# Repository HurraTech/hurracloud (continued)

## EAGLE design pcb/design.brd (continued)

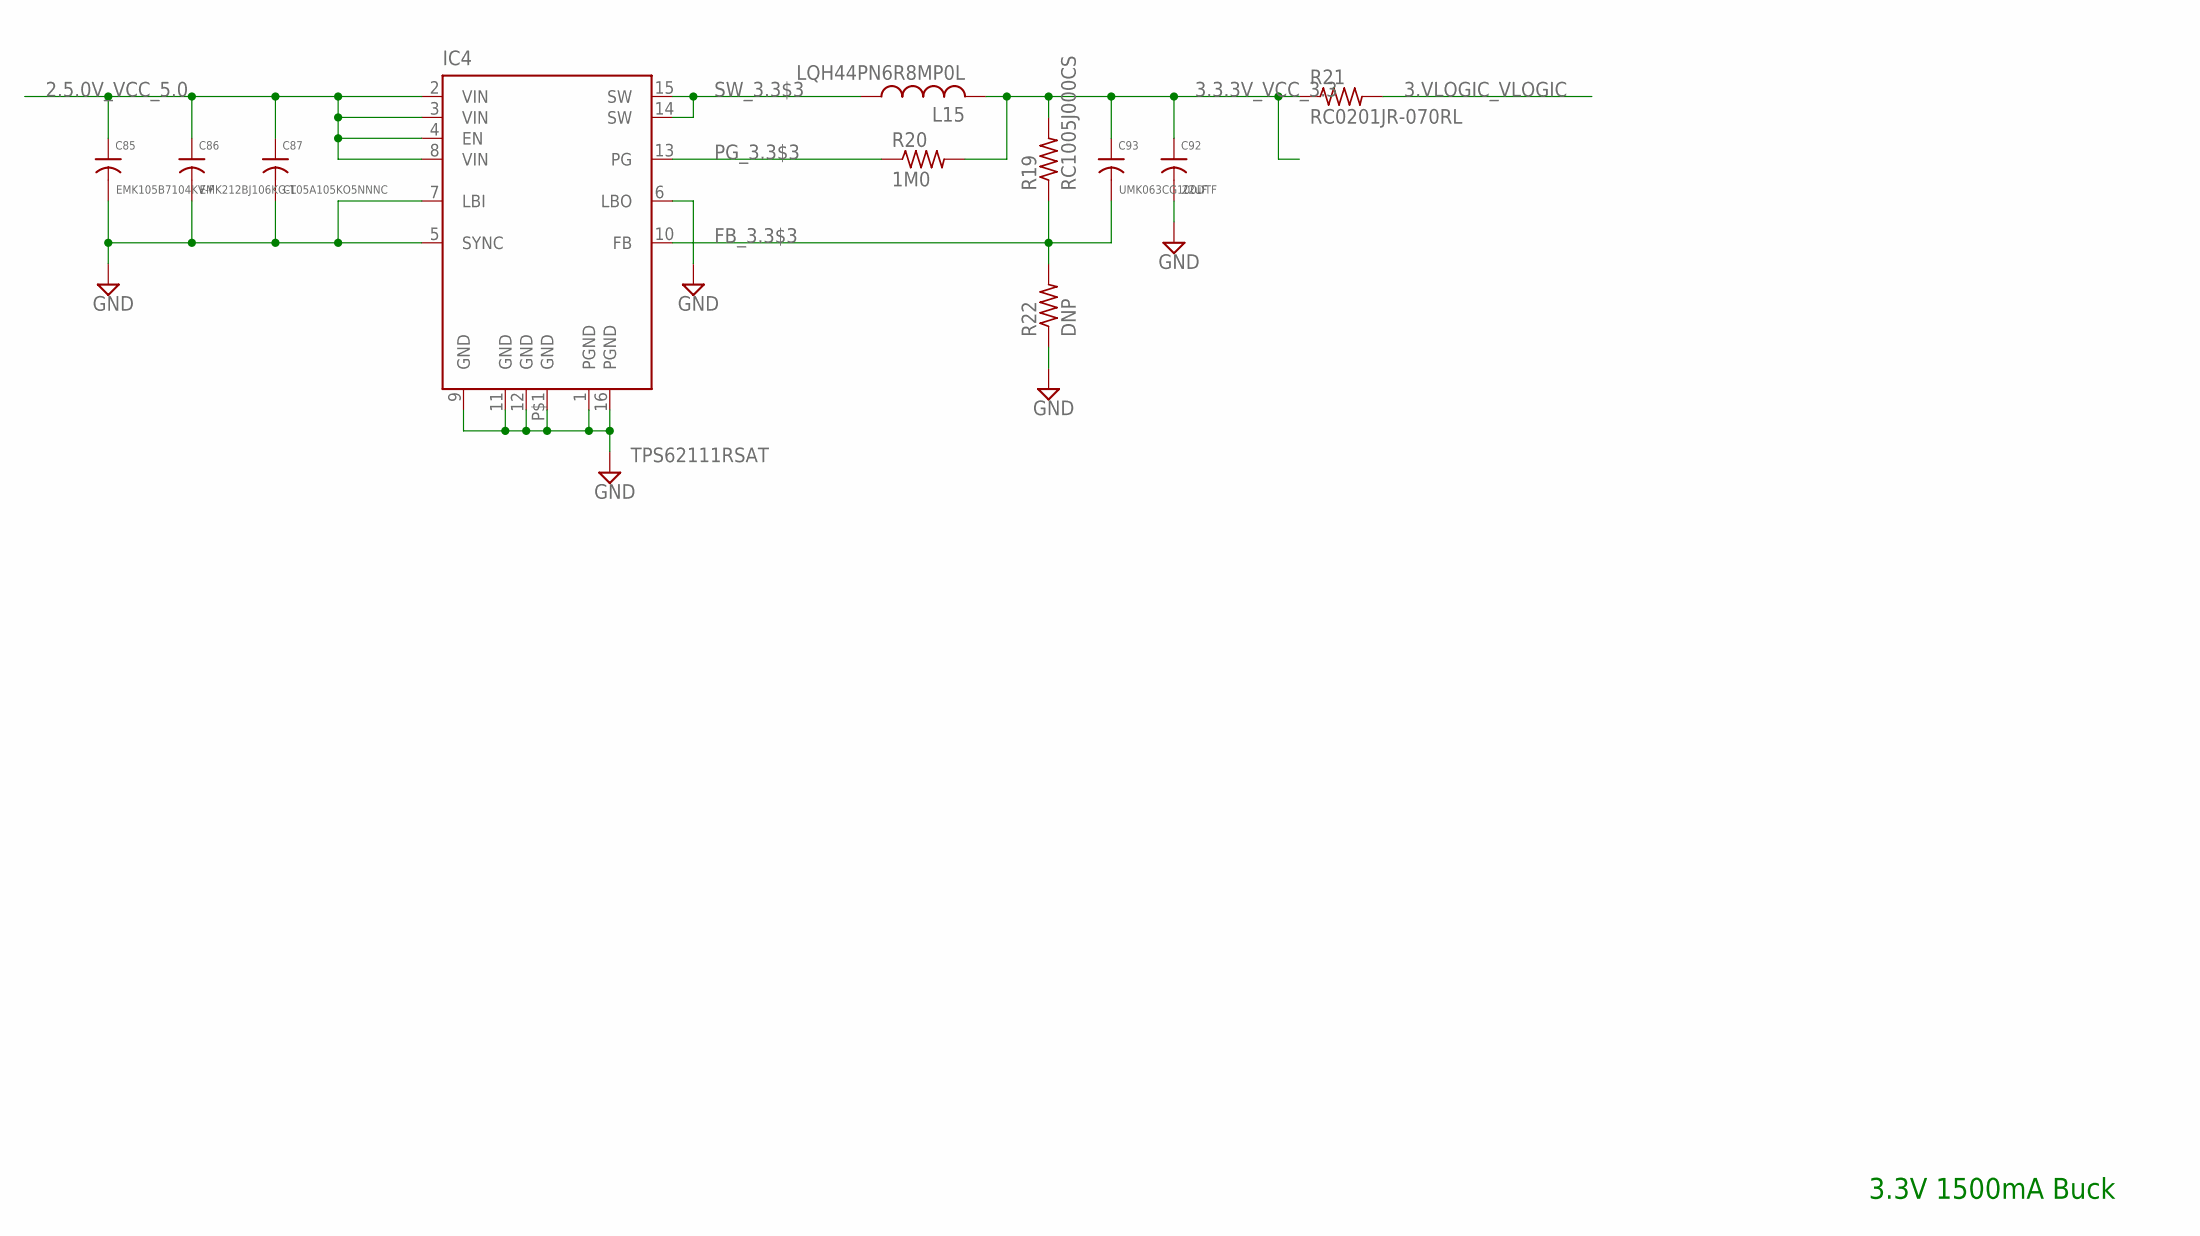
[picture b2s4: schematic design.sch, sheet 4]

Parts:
C85: EMK105B7104KV-F; 0402
C86: EMK212BJ106KG-T; 0805
C87: CL05A105KO5NNNC; 0402
C92: 22uF; 0805
C93: UMK063CG100DTF; 0201
IC4: TPS62111RSAT; PQFP16
L15: LQH44PN6R8MP0L; 1515
R19: RC1005J000CS; 0402
R20: 1M0; 0201
R21: RC0201JR-070RL; 0201
R22: DNP; 0402

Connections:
2.5.0V_VCC_5.0: C85.1, C86.1, C87.1, IC4.2 (VIN), IC4.3 (VIN), IC4.4 (EN), IC4.8 (VIN); also elsewhere on the board
3.3.3V_VCC_3.3: C92.1, C93.1, L15.2, R19.2, R20.2, R21.1; also elsewhere on the board
3.VLOGIC_VLOGIC: R21.2
FB_3.3$3: C93.2, IC4.10 (FB), R19.1, R22.2
GND: C85.2, C86.2, C87.2, C92.2, IC4.1 (PGND), IC4.5 (SYNC), IC4.6 (LBO), IC4.7 (LBI), IC4.9 (GND), IC4.11 (GND), IC4.12 (GND), IC4.16 (PGND), IC4.P$1 (GND), R22.1; also elsewhere on the board
PG_3.3$3: IC4.13 (PG), R20.1
SW_3.3$3: IC4.14 (SW), IC4.15 (SW), L15.1

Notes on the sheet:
3.3V 1500mA Buck

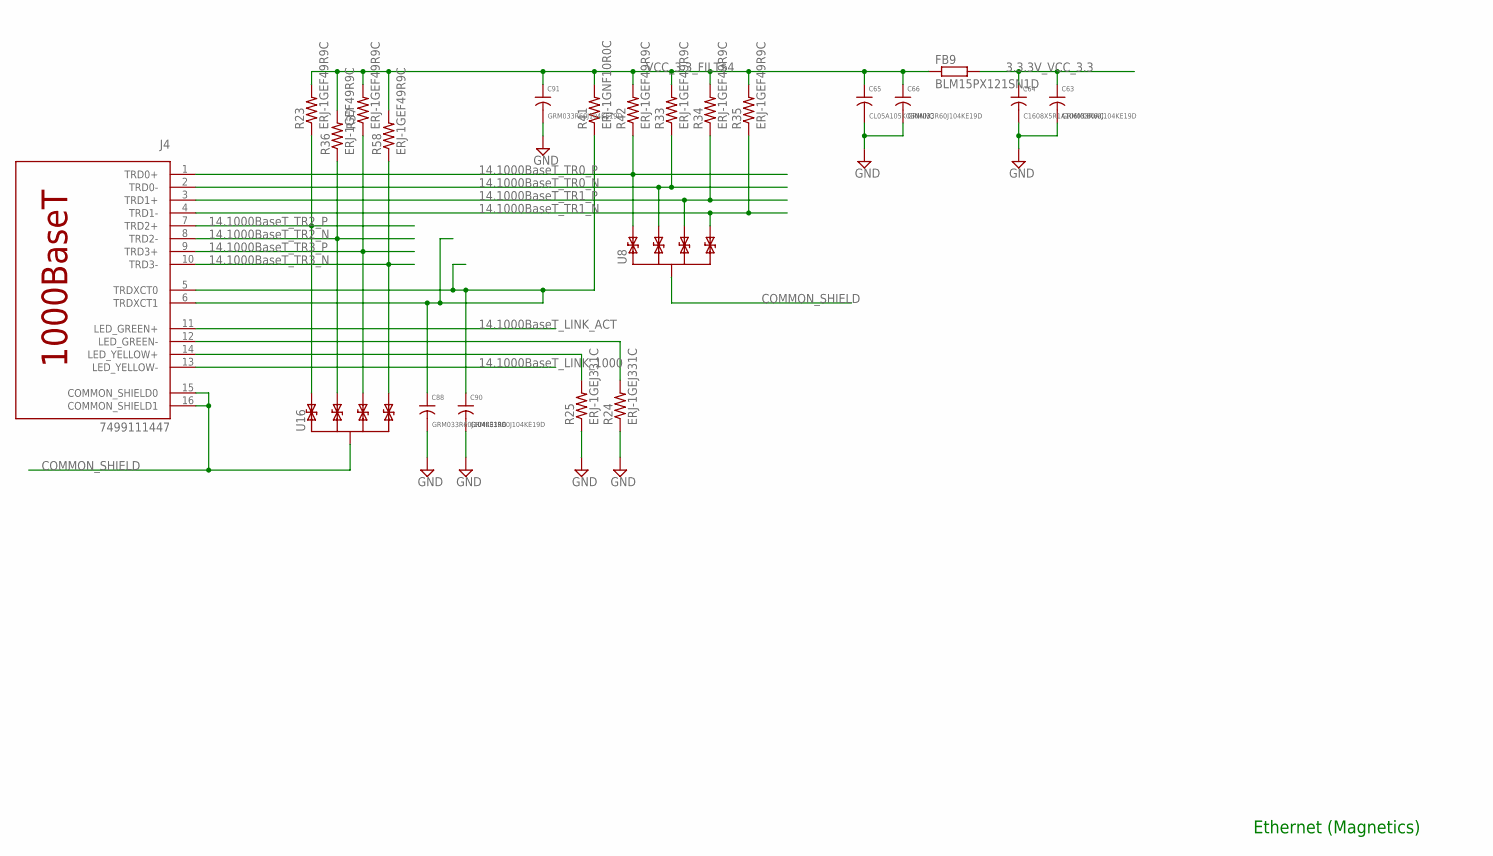
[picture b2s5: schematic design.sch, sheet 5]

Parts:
C63, C66, C88, C90, C91: GRM033R60J104KE19D; 0201
C64: C1608X5R1A106M080AC; 0603
C65: CL05A105KO5NNNC; 0402
FB9: BLM15PX121SN1D; 0402
J4: 7499111447
R23, R33, R34, R35, R36, R37, R42, R58: ERJ-1GEF49R9C; 0201
R24, R25: ERJ-1GEJ331C; 0201
R41: ERJ-1GNF10R0C; 0201
U8, U16: TPD4E02B04DQAR; UFDFN-10

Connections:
3.3.3V_VCC_3.3: C63.1, C64.1, FB9.2; also elsewhere on the board
14.1000BaseT_LINK_1000: J4.13 (LED_YELLOW-); also elsewhere on the board
14.1000BaseT_LINK_ACT: J4.11 (LED_GREEN+); also elsewhere on the board
14.1000BaseT_TR0_N: J4.2 (TRD0-), R33.1, U8.2, U8.9 (P2); also elsewhere on the board
14.1000BaseT_TR0_P: J4.1 (TRD0+), R42.1, U8.1, U8.10 (P1); also elsewhere on the board
14.1000BaseT_TR1_N: J4.4 (TRD1-), R35.1, U8.5 (P4), U8.6 (P4); also elsewhere on the board
14.1000BaseT_TR1_P: J4.3 (TRD1+), R34.1, U8.4 (P3), U8.7 (P3); also elsewhere on the board
14.1000BaseT_TR2_N: J4.8 (TRD2-), R36.1, U16.2, U16.9 (P2); also elsewhere on the board
14.1000BaseT_TR2_P: J4.7 (TRD2+), R23.1, U16.1, U16.10 (P1); also elsewhere on the board
14.1000BaseT_TR3_N: J4.10 (TRD3-), R58.1, U16.5 (P4), U16.6 (P4); also elsewhere on the board
14.1000BaseT_TR3_P: J4.9 (TRD3+), R37.1, U16.4 (P3), U16.7 (P3); also elsewhere on the board
COMMON_SHIELD: J4.15 (COMMON_SHIELD0), J4.16 (COMMON_SHIELD1), U8.3 (SHIELD), U8.8 (SHIELD), U16.3 (SHIELD), U16.8 (SHIELD); also elsewhere on the board
CT0$4: C88.1, C90.1, J4.5 (TRDXCT0), J4.6 (TRDXCT1), R41.1
GND: C63.2, C64.2, C65.2, C66.2, C88.2, C90.2, C91.2, R24.1, R25.1; also elsewhere on the board
LED_GREEN_N$4: J4.12 (LED_GREEN-), R24.2
LED_YELLOW_P$4: J4.14 (LED_YELLOW+), R25.2
VCC_3.3_FILT$4: C65.1, C66.1, C91.1, FB9.1, R23.2, R33.2, R34.2, R35.2, R36.2, R37.2, R41.2, R42.2, R58.2

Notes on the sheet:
Ethernet (Magnetics)

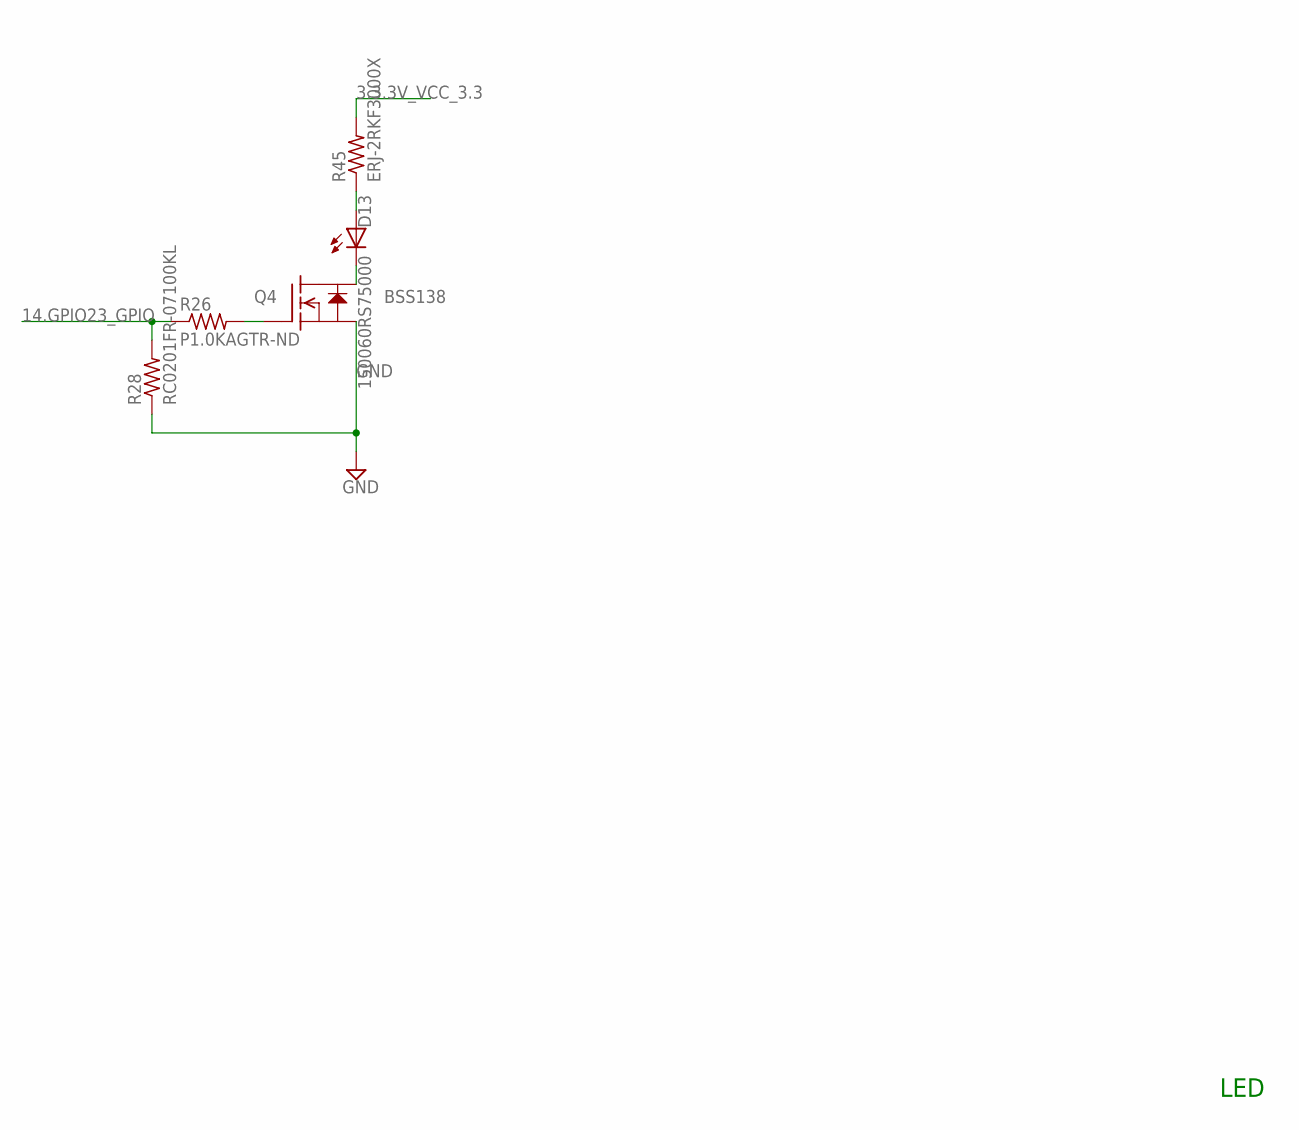
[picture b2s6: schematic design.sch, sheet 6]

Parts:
D13: 150060RS75000; D0603
Q4: BSS138; SOT23
R26: P1.0KAGTR-ND; 0201
R28: RC0201FR-07100KL; 0201
R45: ERJ-2RKF3000X; 0402

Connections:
3.3.3V_VCC_3.3: R45.2; also elsewhere on the board
14.GPIO23_GPIO: R26.1, R28.2; also elsewhere on the board
ANODE$9: D13.A, R45.1
GATE$9: Q4.1 (G), R26.2
GND: Q4.2 (S), R28.1; also elsewhere on the board
LED-$9: D13.C, Q4.3 (D)

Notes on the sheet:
LED

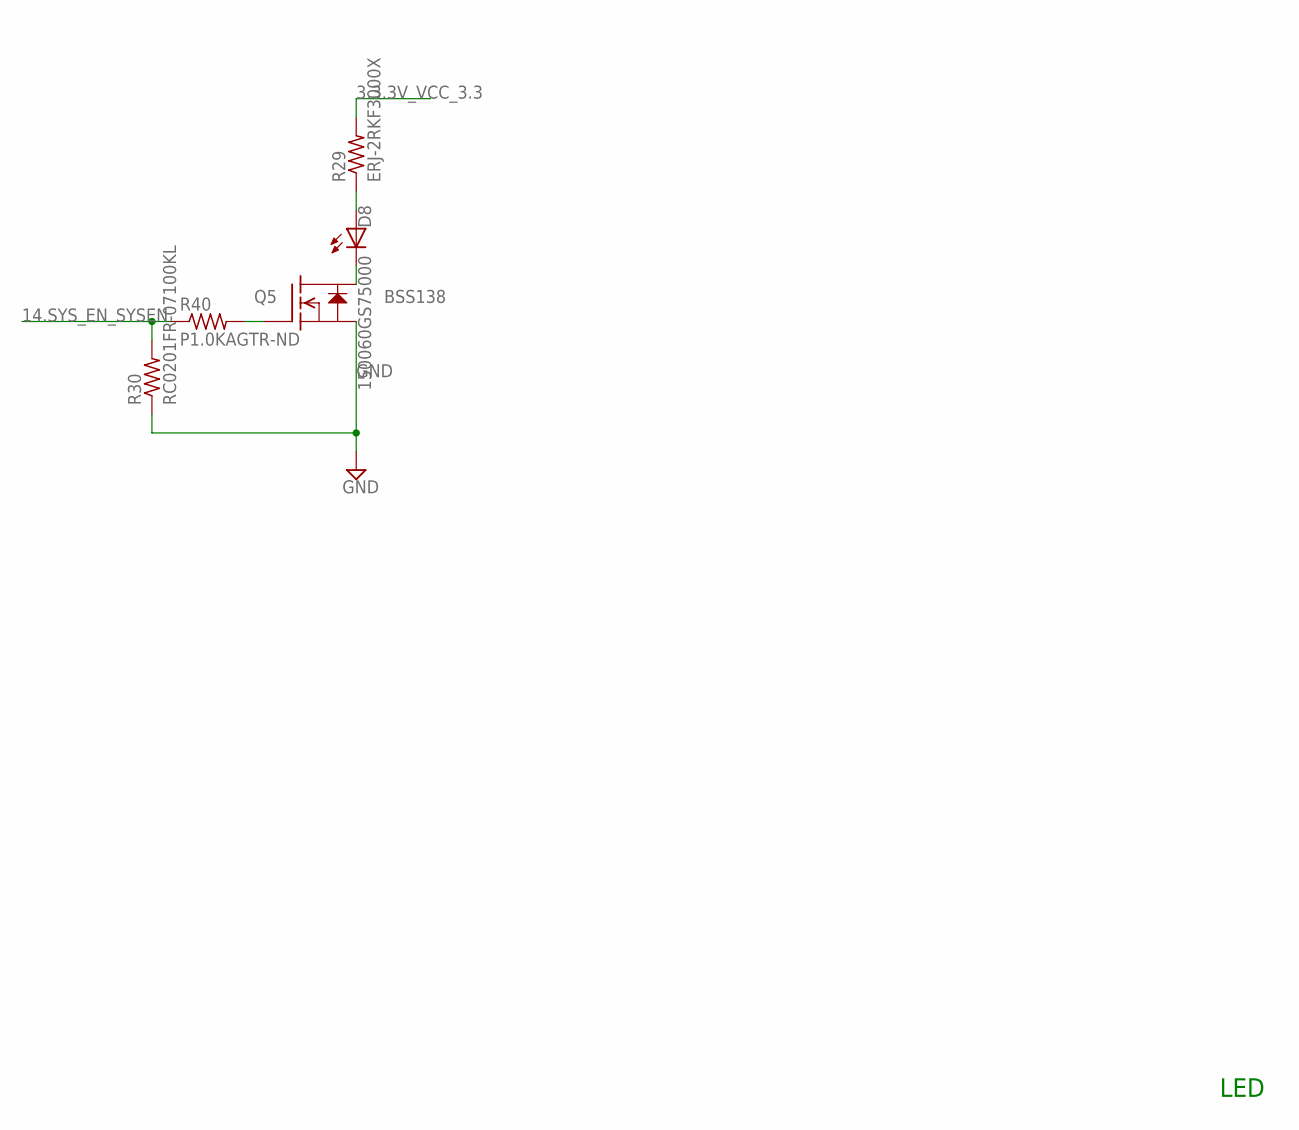
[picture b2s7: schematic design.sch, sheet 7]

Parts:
D8: 150060GS75000; D0603
Q5: BSS138; SOT23
R29: ERJ-2RKF3000X; 0402
R30: RC0201FR-07100KL; 0201
R40: P1.0KAGTR-ND; 0201

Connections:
3.3.3V_VCC_3.3: R29.2; also elsewhere on the board
14.SYS_EN_SYSEN: R30.2, R40.1; also elsewhere on the board
ANODE$10: D8.A, R29.1
GATE$10: Q5.1 (G), R40.2
GND: Q5.2 (S), R30.1; also elsewhere on the board
LED-$10: D8.C, Q5.3 (D)

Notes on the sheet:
LED

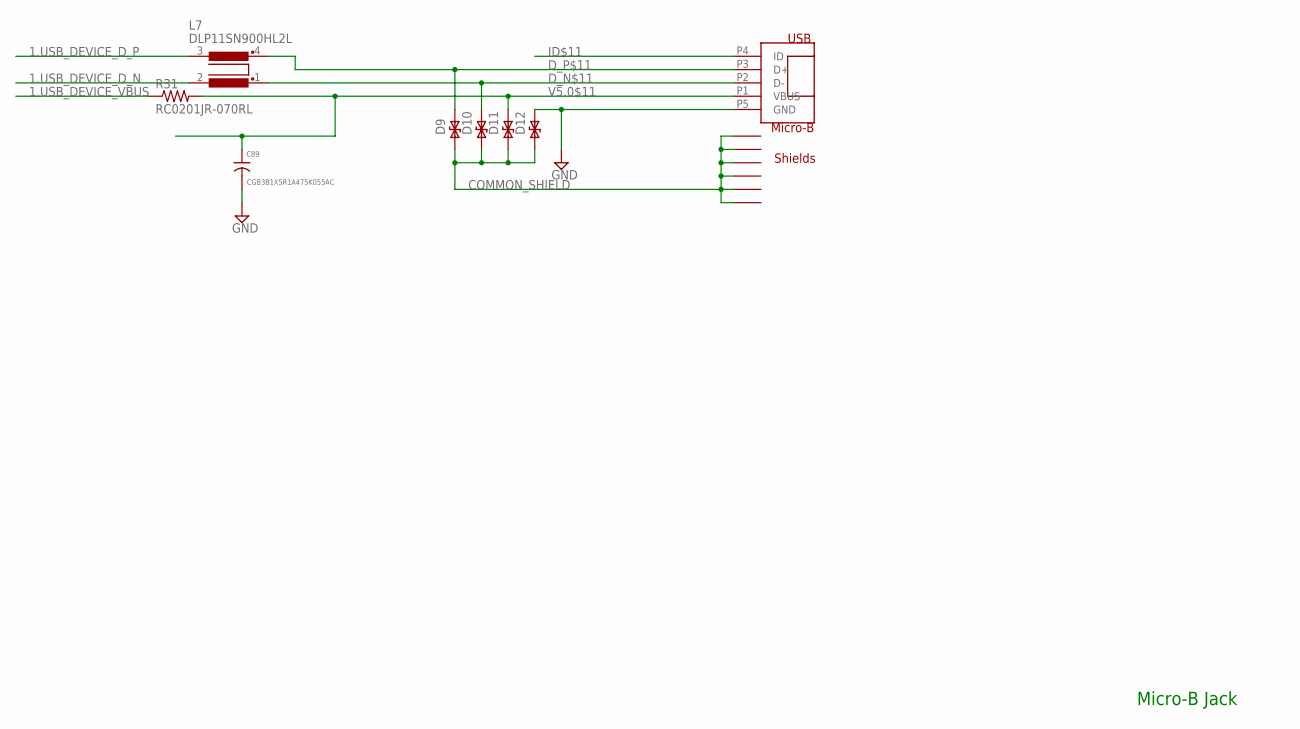
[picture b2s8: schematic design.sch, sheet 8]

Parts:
C89: CGB3B1X5R1A475K055AC; 0603
D9, D10: PS04LTVA1; D0402
D11, D12: B72590D0050A060; D0402
J3: 10118192-0001LF; USB_MICRO_B
L7: DLP11SN900HL2L; 0504-DLP11S
R31: RC0201JR-070RL; 0201

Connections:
1.USB_DEVICE_D_N: L7.2; also elsewhere on the board
1.USB_DEVICE_D_P: L7.3; also elsewhere on the board
1.USB_DEVICE_VBUS: R31.1; also elsewhere on the board
COMMON_SHIELD: D9.P1, D10.P1, D11.P1, D12.P1, J3.COMMON_SHEILD1 (COMMON_SHIELD1), J3.COMMON_SHEILD2 (COMMON_SHIELD2), J3.COMMON_SHEILD3 (COMMON_SHIELD3), J3.COMMON_SHEILD4 (COMMON_SHIELD4), J3.COMMON_SHEILD5 (COMMON_SHIELD5), J3.COMMON_SHEILD6 (COMMON_SHIELD6); also elsewhere on the board
D_N$11: D10.P2, J3.P2 (D-), L7.1
D_P$11: D9.P2, J3.P3 (D+), L7.4
GND: C89.2, D12.P2, J3.P5 (GND); also elsewhere on the board
ID$11: J3.P4 (ID)
V5.0$11: C89.1, D11.P2, J3.P1 (VBUS), R31.2

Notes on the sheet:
Micro-B Jack

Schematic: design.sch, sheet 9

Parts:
C94, C95, C258, C259, C271: GRM033R60J104KE19D; 0201
C257, C261: GRM033R61C103KA12D; 0201
L8, L9, L12, L13: DLP11SN900HL2L; 0504-DLP11S
R43: CRCW040275R0FKEDC; 0402
RP3: DNP; 741X08
U9: TPD13S523PWR; TSSOP16
U14: 685119134923; 47151-001
U$24: TXS0104ERGYR; S-PVQFN-N14

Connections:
2.5.0V_VCC_5.0: C258.1, C259.1, U9.5 (5V_SUPPLY), U$24.14 (VCCB); also elsewhere on the board
14.HDMI0_CEC: RP3.4, U$24.2 (A1); also elsewhere on the board
14.HDMI0_CLOCK_N: L9.2, U9.9 (D3-); also elsewhere on the board
14.HDMI0_CLOCK_P: L9.3, U9.10 (D3+); also elsewhere on the board
14.HDMI0_D0_N: L8.2, U9.11 (D2-); also elsewhere on the board
14.HDMI0_D0_P: L8.3, U9.12 (D2+); also elsewhere on the board
14.HDMI0_D1_N: L13.2, U9.13 (D1-); also elsewhere on the board
14.HDMI0_D1_P: L13.3, U9.14 (D1+); also elsewhere on the board
14.HDMI0_D2_N: L12.2, U9.15 (D0-); also elsewhere on the board
14.HDMI0_D2_P: L12.3, U9.16 (D0+); also elsewhere on the board
14.HDMI0_DDC_SCL: RP3.3, U$24.3 (A2); also elsewhere on the board
14.HDMI0_DDC_SDA: RP3.2, U$24.4 (A3); also elsewhere on the board
14.HDMI0_HPD: RP3.1, U$24.5 (A4); also elsewhere on the board
14.VLOGIC_VLOGIC: C95.1, C257.1, C261.1, C271.1, U$24.1 (VCCA), U$24.8 (OE); also elsewhere on the board
CEC$12: RP3.5, U9.1 (CTRL1), U14.13, U$24.13 (B1)
COMMON_SHIELD: U14.G1 (20), U14.G2 (21), U14.G3 (22), U14.G4 (23); also elsewhere on the board
CON_5V0$12: C94.1, U9.6 (5V_OUT), U14.18
DDC_SCL$12: RP3.6, U9.2 (CTRL2), U14.15, U$24.12 (B2)
DDC_SDA$12: RP3.7, U9.3 (CTRL3), U14.16, U$24.11 (B3)
GND: C94.2, C95.2, C257.2, C258.2, C259.2, C261.2, C271.2, R43.1, U9.8 (GND), U14.2, U14.5, U14.8, U14.11, U14.17, U$24.7 (GND); also elsewhere on the board
HPD$12: RP3.8, U9.4 (CTRL4), U14.19, U$24.10 (B4)
TXD0_CONN_N$12: L8.1, U14.9
TXD0_CONN_P$12: L8.4, U14.7
TXD1_CONN_N$12: L13.1, U14.6
TXD1_CONN_P$12: L13.4, U14.4
TXD2_CONN_N$12: L12.1, U14.3
TXD2_CONN_P$12: L12.4, U14.1
TXDC_CONN_N$12: L9.1, U14.12
TXDC_CONN_P$12: L9.4, U14.10
UTIL$12: R43.2, U9.7 (CTRL5), U14.14

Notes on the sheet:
HDMI

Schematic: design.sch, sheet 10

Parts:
C256: GRM033R60J104KE19D; 0201
R38: RC0201FR-0710KL; 0201
R39: RC0201JR-070RL; 0201
RP1, RP2: DNP; RP741X083
U19: TS3A5223RSWR; UQFN-10

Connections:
13.UART1_RXD: RP1.1, U19.7 (NC2); also elsewhere on the board
13.UART1_TXD: RP1.2, U19.5 (NC1); also elsewhere on the board
13.UART2_RXD: RP2.4, U19.10 (NO2); also elsewhere on the board
13.UART2_TXD: RP2.3, U19.2 (NO1); also elsewhere on the board
13.VLOGIC_OUT_VLOGIC: R39.2; also elsewhere on the board
14.UART0_RXD: RP1.8, RP2.5, U19.9 (COM2); also elsewhere on the board
14.UART0_TXD: RP1.7, RP2.6, U19.3 (COM1); also elsewhere on the board
14.USB3_CC2_GPIO: R38.2, U19.4 (SEL1), U19.8 (SEL2); also elsewhere on the board
14.VLOGIC_VLOGIC: C256.1, R39.1, U19.1 (VCC); also elsewhere on the board
GND: C256.2, R38.1, U19.6 (GND); also elsewhere on the board

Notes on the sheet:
Quad 2 Input MUX

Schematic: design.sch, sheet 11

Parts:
J2, J5: DF40C-100DS-0.4V(51); HRS_DF40C-100DS-0.4V(51)
MP1, MP2, MP3, MP4: 9774015151R; WA-SMSI_9774___151
Q1: BSS138; SOT23
Q2, Q3: FDN360P; SOT23
R44, R49, R50: RC0201JR-070RL; 0201
R48: DNP; 0201
R51: RC0201FR-0710KL; 0201

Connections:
1.8V_OUT$14: J5.88, J5.90, R48.1
2.5.0V_VCC_5.0: J5.77, J5.79, J5.81, J5.83, J5.85, J5.87; also elsewhere on the board
3.3V_OUT$14: J5.84, J5.86, Q2.3 (D), R44.1, R50.1
14.3.3V_VCC_3.3: Q3.3 (D), R49.2; also elsewhere on the board
14.1000BaseT_LINK_100: J5.19
14.1000BaseT_LINK_1000: J5.17; also elsewhere on the board
14.1000BaseT_LINK_ACT: J5.15; also elsewhere on the board
14.1000BaseT_TR0_N: J5.10; also elsewhere on the board
14.1000BaseT_TR0_P: J5.12; also elsewhere on the board
14.1000BaseT_TR1_N: J5.6; also elsewhere on the board
14.1000BaseT_TR1_P: J5.4; also elsewhere on the board
14.1000BaseT_TR2_N: J5.9; also elsewhere on the board
14.1000BaseT_TR2_P: J5.11; also elsewhere on the board
14.1000BaseT_TR3_N: J5.5; also elsewhere on the board
14.1000BaseT_TR3_P: J5.3; also elsewhere on the board
14.GPIO2_GPIO: J5.58; also elsewhere on the board
14.GPIO3_GPIO: J5.56; also elsewhere on the board
14.GPIO4_GPIO: J5.54; also elsewhere on the board
14.GPIO5_GPIO: J5.34; also elsewhere on the board
14.GPIO6_GPIO: J5.30; also elsewhere on the board
14.GPIO7_GPIO: J5.37; also elsewhere on the board
14.GPIO8_GPIO: J5.39; also elsewhere on the board
14.GPIO9_GPIO: J5.40; also elsewhere on the board
14.GPIO10_GPIO: J5.44; also elsewhere on the board
14.GPIO11_GPIO: J5.38; also elsewhere on the board
14.GPIO12_GPIO: J5.31; also elsewhere on the board
14.GPIO13_GPIO: J5.28; also elsewhere on the board
14.GPIO16_GPIO: J5.29; also elsewhere on the board
14.GPIO17_GPIO: J5.50; also elsewhere on the board
14.GPIO18_GPIO: J5.49; also elsewhere on the board
14.GPIO19_GPIO: J5.26; also elsewhere on the board
14.GPIO20_GPIO: J5.27; also elsewhere on the board
14.GPIO21_GPIO: J5.25; also elsewhere on the board
14.GPIO22_GPIO: J5.46; also elsewhere on the board
14.GPIO23_GPIO: J5.47; also elsewhere on the board
14.GPIO24_GPIO: J5.45; also elsewhere on the board
14.GPIO25_GPIO: J5.41; also elsewhere on the board
14.GPIO26_GPIO: J5.24; also elsewhere on the board
14.GPIO27_GPIO: J5.48; also elsewhere on the board
14.HDMI0_CEC: J2.51; also elsewhere on the board
14.HDMI0_CLOCK_N: J2.90; also elsewhere on the board
14.HDMI0_CLOCK_P: J2.88; also elsewhere on the board
14.HDMI0_D0_N: J2.84; also elsewhere on the board
14.HDMI0_D0_P: J2.82; also elsewhere on the board
14.HDMI0_D1_N: J2.78; also elsewhere on the board
14.HDMI0_D1_P: J2.76; also elsewhere on the board
14.HDMI0_D2_N: J2.72; also elsewhere on the board
14.HDMI0_D2_P: J2.70; also elsewhere on the board
14.HDMI0_DDC_SCL: J2.100; also elsewhere on the board
14.HDMI0_DDC_SDA: J2.99; also elsewhere on the board
14.HDMI0_HPD: J2.53; also elsewhere on the board
14.I2C_ID_SCL: J5.35; also elsewhere on the board
14.I2C_ID_SDA: J5.36; also elsewhere on the board
14.PCIE_CLKREQ_GPIO: J2.2; also elsewhere on the board
14.PCIE_CLK_N: J2.12; also elsewhere on the board
14.PCIE_CLK_P: J2.10; also elsewhere on the board
14.PCIE_RST_GPIO: J2.9; also elsewhere on the board
14.PCIE_RX0_N: J2.18; also elsewhere on the board
14.PCIE_RX0_P: J2.16; also elsewhere on the board
14.PCIE_TX0_N: J2.24; also elsewhere on the board
14.PCIE_TX0_P: J2.22; also elsewhere on the board
14.SYS_EN_SYSEN: J5.100, Q1.1 (G), R51.2; also elsewhere on the board
14.UART0_RXD: J5.51; also elsewhere on the board
14.UART0_TXD: J5.55; also elsewhere on the board
14.USB3_CC1_GPIO: J5.94; also elsewhere on the board
14.USB3_CC2_GPIO: J5.96; also elsewhere on the board
14.USB_HOST_DRV_VBUS: R50.2; also elsewhere on the board
14.USB_HOST_D_N: J2.3; also elsewhere on the board
14.USB_HOST_D_P: J2.5; also elsewhere on the board
14.VLOGIC_VLOGIC: R49.1; also elsewhere on the board
14.nRESET_NRESET: J5.92; also elsewhere on the board
!RPIBOOT$14: J5.93
DS_LOAD$14: Q2.2 (S), Q3.2 (S)
EEPROM_!WP: J5.20
ETH_SYNC_IN: J5.16
ETH_SYNC_OUT: J5.18
GLOBAL_EN: J5.99
GND: J2.7, J2.8, J2.13, J2.14, J2.19, J2.20, J2.25, J2.26, J2.31, J2.32, J2.37, J2.38, J2.44, J2.50, J2.55, J2.56, J2.61, J2.62, J2.67, J2.68, J2.73, J2.74, J2.79, J2.80, J2.85, J2.86, J2.91, J2.92, J2.97, J2.98, J5.1, J5.2, J5.7, J5.8, J5.13, J5.14, J5.22, J5.23, J5.32, J5.33, J5.42, J5.43, J5.52, J5.53, J5.59, J5.60, J5.65, J5.66, J5.71, J5.74, J5.98, MP1.1, MP2.1, MP3.1, MP4.1, Q1.2 (S), R51.1; also elsewhere on the board
GPIO_VREF$14: J5.78, R44.2, R48.2; also elsewhere on the board
LOAD_GATE$14: Q1.3 (D), Q2.1 (G), Q3.1 (G)
PI_!LED_ACT: J5.21
PI_LED_!PWR: J5.95
SD_CLK: J5.57
SD_CMD: J5.62
SD_DAT0: J5.63
SD_DAT1: J5.67
SD_DAT2: J5.69
SD_DAT3: J5.61
SD_DAT4: J5.68
SD_DAT5: J5.64
SD_DAT6: J5.72
SD_DAT7: J5.70
SD_PWR_ON: J5.75
SD_VDD_OV: J5.73
VDAC_COMP: J2.11

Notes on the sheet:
Raspberry Pi CM4
GPIO
High Speed

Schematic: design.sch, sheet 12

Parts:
C260: GRM033R60J104KE19D; 0201
IC5: CAT24C256YI-GT3; TSSOP8
R52, R53, R54: RC0201FR-07100KL; 0201
R56, R57: ERJ-1GNJ152C; 0201

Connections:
14.I2C_ID_SCL: IC5.6 (SCL), R57.1; also elsewhere on the board
14.I2C_ID_SDA: IC5.5 (SDA), R56.1; also elsewhere on the board
A0$14: IC5.1 (A0), R54.2
A1$14: IC5.2 (A1), R53.2
A2$14: IC5.3 (A2), R52.2
GND: C260.2, IC5.4 (GND), IC5.7 (WP), R52.1, R53.1; also elsewhere on the board
GPIO_VREF$14: C260.1, IC5.8 (VCC), R54.1, R56.2, R57.2; also elsewhere on the board

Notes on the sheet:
Raspberry Pi CM4

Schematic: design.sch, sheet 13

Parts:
U12: 67996-140HLF; 2X20

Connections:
2.5.0V_VCC_5.0: U12.2, U12.4; also elsewhere on the board
3.3.3V_VCC_3.3: U12.17; also elsewhere on the board
13.UART1_RXD: U12.10; also elsewhere on the board
13.UART1_TXD: U12.8; also elsewhere on the board
14.3.3V_VCC_3.3: U12.1; also elsewhere on the board
14.GPIO2_GPIO: U12.3; also elsewhere on the board
14.GPIO3_GPIO: U12.5; also elsewhere on the board
14.GPIO4_GPIO: U12.7; also elsewhere on the board
14.GPIO5_GPIO: U12.29; also elsewhere on the board
14.GPIO6_GPIO: U12.31; also elsewhere on the board
14.GPIO7_GPIO: U12.26; also elsewhere on the board
14.GPIO8_GPIO: U12.24; also elsewhere on the board
14.GPIO9_GPIO: U12.21; also elsewhere on the board
14.GPIO10_GPIO: U12.19; also elsewhere on the board
14.GPIO11_GPIO: U12.23; also elsewhere on the board
14.GPIO12_GPIO: U12.32; also elsewhere on the board
14.GPIO13_GPIO: U12.33; also elsewhere on the board
14.GPIO16_GPIO: U12.36; also elsewhere on the board
14.GPIO17_GPIO: U12.11; also elsewhere on the board
14.GPIO18_GPIO: U12.12; also elsewhere on the board
14.GPIO19_GPIO: U12.35; also elsewhere on the board
14.GPIO20_GPIO: U12.38; also elsewhere on the board
14.GPIO21_GPIO: U12.40; also elsewhere on the board
14.GPIO22_GPIO: U12.15; also elsewhere on the board
14.GPIO23_GPIO: U12.16; also elsewhere on the board
14.GPIO24_GPIO: U12.18; also elsewhere on the board
14.GPIO25_GPIO: U12.22; also elsewhere on the board
14.GPIO26_GPIO: U12.37; also elsewhere on the board
14.GPIO27_GPIO: U12.13; also elsewhere on the board
14.I2C_ID_SCL: U12.28; also elsewhere on the board
14.I2C_ID_SDA: U12.27; also elsewhere on the board
GND: U12.6, U12.9, U12.14, U12.20, U12.25, U12.30, U12.34, U12.39; also elsewhere on the board

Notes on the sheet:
40-Pin Header

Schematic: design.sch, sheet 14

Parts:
C41, C42, C43, C44, C253, C254, C263, C264, C265, C266, C267, C268, C269, C273, C280, C281, C286, C287, C288, C289: GRM033R60J104KE19D; 0201
C45, C46: C1608X5R1A106M080AC; 0603
C158, C167: CGB3B1X5R1A475K055AC; 0603
C270: GRM033R71A682KA01D; 0201
C282, C283: C1608X5R1C475K080AC; 0603
C285: UMK063CG100DTF; 0201
R27, R55: RC0201FR-0710KL; 0201
R32: RC0201FR-0712K1L; 0201
R47: RC0201FR-07100KL; 0201
U10: ASM1142; QFN64-9X9MM-FT2232HQ
U18: ADP1740ACPZ-1.2-R7; LFCSPWQ16
Y3: ABM8G-20.000MHZ-18-D2Y-T; CRYSTAL-3225

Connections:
3.3.3V_VCC_3.3: C41.1, C42.1, C45.1, C158.1, C267.1, C268.1, C269.1, C280.1, C286.1, C287.1, R27.2, R47.2, R55.2, U10.4 (VCC), U10.20 (VCCSUS), U10.24 (VCCSUS), U10.32 (VCC), U10.38 (VCCU), U10.44 (VCCU), U10.55 (VCCP), U10.62 (VCCP), U18.1 (VIN), U18.2 (VIN), U18.3 (VIN), U18.4 (EN), U18.15 (VIN), U18.16 (VIN); also elsewhere on the board
14.PCIE_CLKREQ_GPIO: R27.1, U10.9 (!PORST); also elsewhere on the board
14.PCIE_CLK_N: U10.49 (PCIE_REFCLK_N); also elsewhere on the board
14.PCIE_CLK_P: U10.48 (PCIE_REFCLK_P); also elsewhere on the board
14.PCIE_RST_GPIO: R55.1, U10.30 (!PERST); also elsewhere on the board
14.PCIE_RX0_N: C273.1; also elsewhere on the board
14.PCIE_RX0_P: C263.1; also elsewhere on the board
14.PCIE_TX0_N: C253.1; also elsewhere on the board
14.PCIE_TX0_P: C254.1; also elsewhere on the board
16.USBH1_DRV_VBUS: U10.26 (PWRON1)
16.USBH1_D_N: U10.22 (USB1_N); also elsewhere on the board
16.USBH1_D_P: U10.23 (USB1_P); also elsewhere on the board
16.USBH1_NOC: U10.28 (!OC1)
16.USBH1_SSRX_N: U10.46 (USB1_SSRX_N); also elsewhere on the board
16.USBH1_SSRX_P: U10.45 (USB1_SSRX_P); also elsewhere on the board
16.USBH1_SSTX_N: U10.43 (USB1_SSTX_N); also elsewhere on the board
16.USBH1_SSTX_P: U10.42 (USB1_SSTX_P); also elsewhere on the board
16.USBH2_DRV_VBUS: U10.27 (PWRON2); also elsewhere on the board
16.USBH2_D_N: U10.18 (USB2_N); also elsewhere on the board
16.USBH2_D_P: U10.19 (USB2_P); also elsewhere on the board
16.USBH2_NOC: U10.29 (!OC2); also elsewhere on the board
16.USBH2_SSRX_N: U10.37 (USB2_SSRX_N); also elsewhere on the board
16.USBH2_SSRX_P: U10.36 (USB2_SSRX_P); also elsewhere on the board
16.USBH2_SSTX_N: U10.40 (USB2_SSTX_N); also elsewhere on the board
16.USBH2_SSTX_P: U10.39 (USB2_SSTX_P); also elsewhere on the board
!SPI_CS$16: U10.7 (!SPI_CS)
GND: C41.2, C42.2, C43.2, C44.2, C45.2, C46.2, C158.2, C167.2, C264.2, C265.2, C266.2, C267.2, C268.2, C269.2, C270.2, C280.2, C281.2, C282.2, C283.2, C286.2, C287.2, C288.2, C289.2, R32.1, U10.15 (GND), U10.65 (GND), U10.EPAD1 (GND), U10.EPAD2 (GND), U10.EPAD3 (GND), U10.EPAD4 (GND), U10.EPAD5 (GND), U10.EPAD6 (GND), U10.EPAD7 (GND), U10.EPAD8 (GND), U10.EPAD9 (GND), U10.EPAD10 (GND), U10.EPAD11 (GND), U10.EPAD12 (GND), U18.6 (GND), U18.EP (GND), U18.EP1 (GND), U18.EP2 (GND), U18.EP3 (GND), U18.EP4 (GND), Y3.2, Y3.4; also elsewhere on the board
PCIE_RX0_N$16: C273.2, U10.57 (PCIE_TX0_N)
PCIE_RX0_P$16: C263.2, U10.56 (PCIE_TX0_P)
PCIE_TX0_N$16: C253.2, U10.54 (PCIE_RX0_N)
PCIE_TX0_P$16: C254.2, U10.53 (PCIE_RX0_P)
REXT$16: R32.2, U10.59 (REXT)
SPI_CLK$16: U10.5 (SPI_CLK)
SPI_DI$16: U10.8 (SPI_DI)
SPI_DO$16: U10.6 (SPI_DO)
UART_RX$16: U10.10 (UART_RX)
UART_TX$16: U10.11 (UART_TX)
V1.2$16: C43.1, C44.1, C46.1, C167.1, C264.1, C265.1, C266.1, C281.1, C282.1, C283.1, C288.1, C289.1, U10.1 (VDD), U10.12 (VDD), U10.21 (VDDSUS), U10.33 (VDD), U10.34 (VDDSUS), U10.35 (VDDU), U10.41 (VDDU), U10.47 (VDDU), U10.52 (VDDP), U10.58 (VDDP), U18.9 (SENSE), U18.10 (VOUT), U18.11 (VOUT), U18.12 (VOUT), U18.13 (VOUT), U18.14 (VOUT)
VCC1V1_SS$16: C270.1, U18.7 (SS)
VCC_1V2_PG$16: R47.1, U18.5 (PG)
XI$16: C285.2, U10.51 (XI), Y3.1
XO$16: C285.1, U10.50 (XO), Y3.3

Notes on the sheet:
PCIe to USB3.0

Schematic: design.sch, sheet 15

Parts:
C272: GRM033R60J104KE19D; 0201
C274: GRM033R61C103KA12D; 0201
C275: C1608X5R1A106M080AC; 0603
C276, C278: DNP; 1206
C277, C279: GRM31CR60J227ME11L; 1206
D2, D5, D6, D15: PS04LTVA1; D0402
D3, D4, D7: B72590D0050A060; D0402
FB11, FB12, FB13, FB14: BLM15PX121SN1D; 0402
K1: 61400826021
L10, L11: DLP11SN900HL2L; 0504-DLP11S
U11: TPS2052BDGNR; MSOP8-PAD

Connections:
2.5.0V_VCC_5.0: C272.1, FB11.1; also elsewhere on the board
18.USBH1_DRV_VBUS: U11.3 (EN1); also elsewhere on the board
18.USBH1_D_N: L10.2; also elsewhere on the board
18.USBH1_D_P: L10.3; also elsewhere on the board
18.USBH1_NOC: U11.8 (NOC1); also elsewhere on the board
18.USBH1_VBUS: D3.P2, FB14.2, U11.7 (OUT1)
18.USBH2_DRV_VBUS: U11.4 (EN2); also elsewhere on the board
18.USBH2_D_N: L11.2; also elsewhere on the board
18.USBH2_D_P: L11.3; also elsewhere on the board
18.USBH2_NOC: U11.5 (NOC2); also elsewhere on the board
18.USBH2_VBUS: D7.P2, FB13.2, U11.6 (OUT2)
A_GNDF$17: C274.1, D4.P2, FB12.2, K1.A4 (GND), K1.B4 (GND)
A_USB_D_N$17: D15.P2, K1.A2 (D-), L10.1
A_USB_D_P$17: D2.P2, K1.A3 (D+), L10.4
A_VBUS_$17: C276.1, C277.1, FB14.1, K1.A1 (VCC)
B_USB_D_N$17: D5.P2, K1.B2 (D-), L11.1
B_USB_D_P$17: D6.P2, K1.B3 (D+), L11.4
B_VBUS_$17: C278.1, C279.1, FB13.1, K1.B1 (VCC)
COMMON_SHIELD: D2.P1, D3.P1, D4.P1, D5.P1, D6.P1, D7.P1, D15.P1; also elsewhere on the board
GND: C272.2, C274.2, C275.2, C276.2, C277.2, C278.2, C279.2, FB12.1, K1.5 (SHIELD_A1), K1.6 (SHIELD_A2), K1.7 (SHIELD_B1), K1.8 (SHIELD_B2), U11.1 (GND), U11.TP (GND); also elsewhere on the board
VBUSF$17: C275.1, FB11.2, U11.2 (IN)

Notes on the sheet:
Dual Stacked USB Type A

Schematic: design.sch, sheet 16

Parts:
C12, C14, C290, C291, C292, C293, C297, C298, C307: GRM033R60J104KE19D; 0201
C15, C299, C313: CL05A105KO5NNNC; 0402
C284: DNP; 0402
C300: CGB3B1X5R1A475K055AC; 0603
C301, C302: GRM0335C1H220JA01D; 0201
IC8: DNP; SC70-5
R4: ERJ-1GEF1202C; 0201
R5, R6, R7, R8, R63, R64: RC0201FR-07100KL; 0201
R60: RC0201JR-070RL; 0201
R62: 1M0; 0201
U13: USB2513B-AEZG; QFN36-6X6MM
Y1: ABM8G-24.000MHZ-18-D2Y-T; CRYSTAL-3225

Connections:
2.5.0V_VCC_5.0: C284.1, IC8.1 (OE), IC8.5 (VCC), R60.2; also elsewhere on the board
14.3.3V_VCC_3.3: C291.1, C292.1, C293.1, C297.1, C298.1, C299.1, C300.1, C307.1, R63.1, R64.2, U13.5 (VDD33), U13.10 (VDD33), U13.15 (VDD33), U13.23 (VDD33), U13.29 (VDD33), U13.36 (VDD33); also elsewhere on the board
14.USB_HOST_DRV_VBUS: IC8.2 (I); also elsewhere on the board
14.USB_HOST_D_N: U13.30 (USBDM_UP); also elsewhere on the board
14.USB_HOST_D_P: U13.31 (USBDP_UP); also elsewhere on the board
14.USB_HOST_VBUS: IC8.4 (O), R60.1
18.USBH1_DRV_VBUS: U13.12 (PRTPWR1); also elsewhere on the board
18.USBH1_D_N: U13.1 (USBDM_DN1); also elsewhere on the board
18.USBH1_D_P: U13.2 (USBDP_DN1); also elsewhere on the board
18.USBH1_NOC: U13.13 (OCS_N1); also elsewhere on the board
18.USBH2_DRV_VBUS: U13.16 (PRTPWR2); also elsewhere on the board
18.USBH2_D_N: U13.3 (USBDM_DN2); also elsewhere on the board
18.USBH2_D_P: U13.4 (USBDP_DN2); also elsewhere on the board
18.USBH2_NOC: U13.17 (OCS_N2); also elsewhere on the board
GND: C12.2, C14.2, C15.2, C284.2, C290.2, C291.2, C292.2, C293.2, C297.2, C298.2, C299.2, C300.2, C301.2, C302.2, C307.2, C313.2, IC8.3 (GND), R4.1, R5.1, R6.1, R7.1, R8.1, U13.EPAD (VSS), U13.EXP1 (VSS), U13.EXP2 (VSS), U13.EXP3 (VSS), U13.EXP4 (VSS), U13.EXP5 (VSS), U13.EXP6 (VSS), U13.EXP7 (VSS), U13.EXP8 (VSS), Y1.2, Y1.4; also elsewhere on the board
USB_CRFILT$18: C14.1, C313.1, U13.14 (CRFILT)
USB_HS_IND$18: R6.2, U13.25 (HS_IND/CFG_SEL1)
USB_NRESET$18: C12.1, R64.1, U13.26 (RESET_N)
USB_PLLFILT$18: C15.1, C290.1, U13.34 (PLLFILT)
USB_RBIAS$18: R4.2, U13.35 (RBIAS)
USB_SCL$18: R5.2, U13.24 (SCL/CFG_SEL0)
USB_SDA$18: R8.2, U13.22 (SDA/NON_REM1)
USB_SUSP_IND$18: R7.2, U13.28 (SUSP_IND/NON_REM0)
USB_VBUS_DET$18: R63.2, U13.27 (VBUS_DET)
USB_XTAL1$18: C302.1, R62.2, U13.33 (XTALIN), Y1.3
USB_XTAL2$18: C301.1, R62.1, U13.32 (XTALOUT), Y1.1

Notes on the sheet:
USB Hub
